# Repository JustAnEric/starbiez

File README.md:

# StarbieZ (star-beez)

Starbiez is a redo of the [Starbie](https://github.com/SharKingStudios/Starbie), and boy it packs *serious* power!

You're now getting your own extendible Tamagotchi that can run MANY things, basically sort of like a *Flipper Zero Nano* but without the pentesting tools! (don't go hacking things around town with this... :C)

## What it does

the ESP32-S3 Plus is where I'd start the shift from MCU to CPU, and it's the main driver for this project. With 16 MB of flash and 8 MB of RAM, it's way more than all the classic Tamagotchis that had **1 KB of RAM and ROM**! this Starbie is equipped with greater environmental awareness, audio and just *one more* button that adds so many more possibilities for what can be done with this project.

the environment can be currently measured by these sensors:

* a light dependent resistor on the right front face of the board
* a DHT11 humidity sensor on the top front face of the board
* AND a 6 pin IMU called the MPU6050 at the bottom right of the board!

the outputs on this device are *pretty simple*:
* 128x64 SSD1306 OLED screen
* buzzer/piezo

you provide input to this project by literally just clicking the cherry MX keyboard switches... and the circuitpython software being packaged for this project is considerably extendable being based off of the C++/.INO software. (yes, I'm rewriting/have rewritten it to make it easier for extensions, welcome beginners!)

## Bill of materials

| Part | What it's for | Qty | Unit | Total | Vendor |
| --- | --- | --- | --- | --- | --- |
| [ESP32-S3 Plus](https://www.pakronics.com.au/products/seeed-studio-xiao-esp32s3-plus-20-gpios-2-4ghz-wifi-ble-5-0-8mb-psram-16mb-flash-esp32-s3-dual-core-battery-charge-supported-ss102010671) | Main loop, more GPIO | 1 | $11.50 | $11.50 | [Pakronics](https://www.pakronics.com.au/products/seeed-studio-xiao-esp32s3-plus-20-gpios-2-4ghz-wifi-ble-5-0-8mb-psram-16mb-flash-esp32-s3-dual-core-battery-charge-supported-ss102010671) |
| [Gateron Milky Pro Switches (10pcs)](https://www.aliexpress.com/item/1005006425450443.html) | Switches and satisfying clicks | 1 | $1.06 | $1.06 | [AliExpress](https://www.aliexpress.com/item/1005006425450443.html) |
| [White 128x64 OLED display](https://www.aliexpress.com/item/1005004355547926.html) | The face of Starbiez | 1 | $2.85 | $2.85 | [AliExpress](https://www.aliexpress.com/item/1005004355547926.html) |
| [DHT22 Chip](https://core-electronics.com.au/dht22-temperature-and-relative-humidity-sensor-module.html) | For improved humidity sensing | 1 | $2.38 | $2.38 | [Core Electronics](https://core-electronics.com.au/dht22-temperature-and-relative-humidity-sensor-module.html) |
| [MPU6050 3-axis IMU](https://www.aliexpress.com/item/1005007989748804.html) | For shaking Starbiez | 1 | $2.92 | $2.92 | [Core Electronics](https://www.aliexpress.com/item/1005007989748804.html) |
| [600 Pack of 1/4 Watt 1% Resistors (30 values, 20 of each)](https://core-electronics.com.au/600-pack-of-1-4-watt-1-resistors-30-values-20-of-each.html) | For resistance in the circuit | 1 | $1.87 | $1.87 | [Core Electronics](https://core-electronics.com.au/600-pack-of-1-4-watt-1-resistors-30-values-20-of-each.html) |
| [Light dependent resistor](https://core-electronics.com.au/light-dependent-resistor-ldr.html) | For helping Starbiez sleep | 1 | $0.22 | $0.22 | [Core Electronics](https://core-electronics.com.au/light-dependent-resistor-ldr.html) |
| [Generic buzzer (⌀11 x 9)](https://core-electronics.com.au/piezo-buzzer.html) | For buzzing through menus (sound interactivity and accessibility) | 1 | $0.22 | $0.22 | [Core Electronics](https://core-electronics.com.au/piezo-buzzer.html) |
| [0.100" (2.54 mm) Female Header: 2x8-Pin, Straight](https://core-electronics.com.au/0-100-2-54-mm-female-header-2x8-pin-straight.html) | For GPIO connectivity (if anyone wanted to use this as a devboard) | 1 | $2.16 | $2.16 | [Core Electronics](https://core-electronics.com.au/0-100-2-54-mm-female-header-2x8-pin-straight.html) |
| [Mint Green MA Keycaps for MX Compatible Switches (5pcs)](https://core-electronics.com.au/mint-green-ma-keycaps-for-mx-compatible-switches-5-pack.html) | For topping off the Gateron Milky Pro Switches | 1 | $6.00 | $6.00 | [Core Electronics](https://core-electronics.com.au/mint-green-ma-keycaps-for-mx-compatible-switches-5-pack.html) |
| [JLCPCB Fab](https://jlcpcb.com) | Starbiez PCB | 1 | $11.95 | $11.95 | [JLCPCB](https://jlcpcb.com) |
| **Parts subtotal** | — | — | — | **$43.13** | — |
| **Tax & shipping** | — | — | — | **$27.33** | — |
| **Total** | — | — | — | **$70.46** | — |

## The process of building
### Day 1!

I spent the whole day, and I quite probably went past 4 hours (the actual making time of my board) to include the things that would make it my own...

You can see the **timestamps in the screenshot names**, for journal purposes I didn't replace them with a generic name throughout my processes!

How to interpret them:

* Example: `Screenshot 2026-10-06 064450.png`
* `2026-`: The year
* `10-`: The month
* `06`: The day
* `064450`:
    * `06`: The hour of the day (in AEST/AEDT, since I'm working on it in Australia/Sydney!)
    * `44`: The minute of the hour `06`
    * `50`: The seconds the screenshot was taken at

Hope this helps!

1. I created the project and crafted the schematic from the [tutorial](https://github.com/SharKingStudios/Starbie)

2. I laid out my PCB, creating the star `Edge.Cuts` from a reference image I found on Google first

    and then the satisfying ground layer by the B button...

    Those steps took about 4 hours and 5 minutes, timed by Google stopwatch (thanks search engine monopoly... never mind)

3. One of my first modifications was with changing the MCU from an ESP32-C3 to an ESP32-S3. My first strongest candidate.

    This swap didn't take very long... They're very structurally similar. I made sure to check Seeed's official guides though, just in case I got the pinouts wrong.

4. I included a second sensor, the LDR03 (light-dependent resistor is what LDR stands for) and I made sure to include a fixed resistance of 10kΩ, though this would change later down the track in my realisation an LDR03 is VERY hard to source in the real world today...!

    Here's where I put it, on the right wing of the star :)

5. A lot of organisation, and another output was added! A buzzer or a piezo was inspired by the Sprig's design when I made my Columns game for them (still waiting for approval), and I feel this Tamagotchi would do *really* well with a bit of tunes.

    I put in a little resistor to prevent any surge back to the tiny ESP... yeah it's pretty small.

6. I found a honeycomb SVG on Flaticon and I decided to use it for the two bottom corners of the board to add some more decoration!

    This was also the time I figured out how to get the 3D models into the footprints, I spent a long time trying to figure out how to get into the footprint editor...

7. Realizing there was not enough clearance for poor Switch 3 around J2, I had to make a few changes. And these changes would be for the better, it's now a dev board... :P It's when I made the switch to the ESP32-S3 Plus to get more GPIO. This is when my board started to look a lot more like trace spaghetti, but it's okay... (I am guessing)

    Now there's odd-even 2x8 GPIO female pins on the board, featuring these that go to the ESP32-S3 Plus! Go from right to left if you flip the Starbiez on it's right side:

    | Pin | GPIO |
    |-----|------|
    | 1 (right) | D6 |
    | 2 (left) | D7 |
    | 3 (right) | D10 |
    | 4 (left) | D11 |
    | 5 (right) | D12 |
    | 6 (left) | D13 |
    | 7 (right) | D14 |
    | 8 (left) | D15 |
    | 9 (right) | D16 |
    | 10 (left) | D17 |
    | 11 (right) | SDA (for I2C!) |
    | 12 (left) | D18 |
    | 13 (right) | SCL (for I2C!) |
    | 14 (left) | D19 |
    | 15 (right) | 3V3 output, make sure not to draw too much! |
    | 16 (left) | board GND |

    <details>
    <summary>Pin reference image for you nerds...</summary>

    > ## Front
    >
    > 
    >
    > ## Back
    > 

    </details>

    (*sparkles*!!) The sparkles I got from Claude, I asked it to make a flat monochrome white sparkle SVG graphic I could use... I plastered it onto the board on all the corners. (***THIS GRAPHIC IS NOW OUTSIDE OF THE FINAL REVISION DUE TO HALF LIFE REQUIREMENTS***)

8. Around this time, I was searching for good parts to use on AliExpress, but I found that shipping from China is a *little* bit too expensive for the grant I'm receiving. I then got a little distracted, still worrying myself about whether the light-dependent resistor I've wired up would be correct. More research got me to change it to a generic one, so here's the LDR part I recommend if anyone tries to build this project:

    | Specification | Value |
    |---------------|-------|
    | dark resistance (pitch black, 0 lux) | ~10MΩ |
    | light resistance (10 lux) | 8kΩ to 20kΩ |
    | max dissipation | 100mW
    | form factor | THT ~5mm |
    | ideally... | the GL5528 |

    I also switched the fixed resistance to 100kΩ so the ESP32-S3 Plus receives a more controlled value than in **0.03 V** or completely uncharted territory...

this took me the ENTIRETY of yesterday to build it and some of today to refine it, in retrospect I got up really early some days :| it took me about 1 hour and 22 minutes to write this writeup, according to Hackatime. I hope every viewer likes this project of mine!

### Day 2

I have swapped out the Claude star assets for my own as requested from Hack Club Half Life. It took about 45 minutes to draw the star assets in MS Paint.

I then converted these black paths into an SVG using Inkscape...

And afterwards, I redone the design of the silkscreen by my two hands. This took about 25 minutes.

I also added mounting holes in four places, as you can see.

### Final board renders (courtesy of JLC)

## Software

I extended/am extending CircuitPython for this project for providing user access to an API, you can view my extensions to CircuitPython [here](https://github.com/JustAnEric/starbiez-circuitpython)! It's recommended to use this instead of normal CircuitPython on your ESP32-S3, as you probably won't have access to much easy modifications.

## Ending README

hopefully Hack Club likes this little project of mine, so I can keep developing it more and more... I'm definitely pushing boundaries here with what can be done, but...

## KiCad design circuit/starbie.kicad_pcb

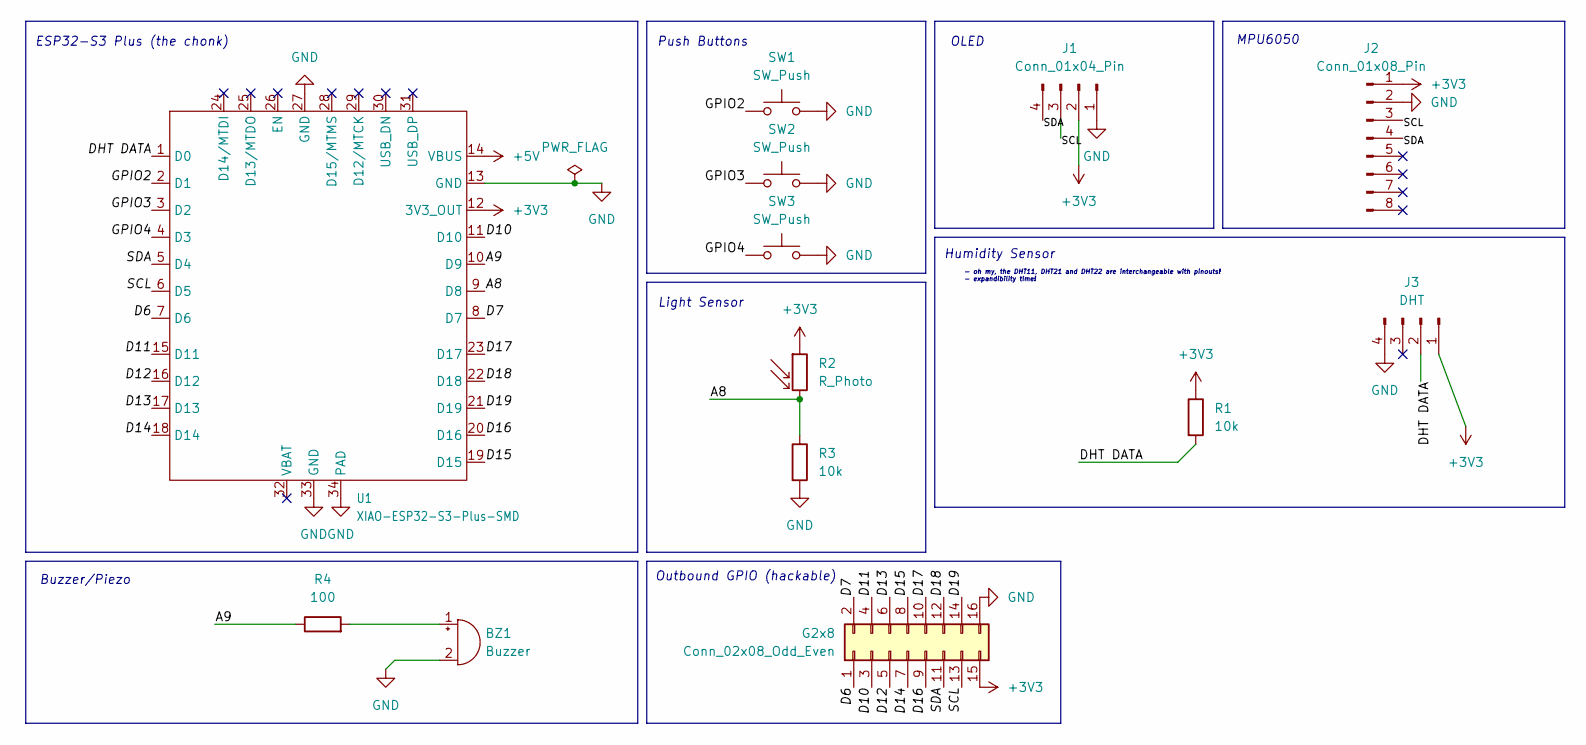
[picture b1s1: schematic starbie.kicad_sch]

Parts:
BZ1: Buzzer; Buzzer_12x9.5RM7.6
G2x8: Conn_02x08_Odd_Even; PinSocket_2x08_P2.54mm_Vertical
J1: Conn_01x04_Pin; Display_128x64_096_I2C
J2: Conn_01x08_Pin; MPU6050_Module
J3: DHT; PinSocket_1x04_P2.54mm_Vertical
R1, R3: 10k; R_Axial_DIN0204_L3.6mm_D1.6mm_P7.62mm_Horizontal
R2: R_Photo; R_LDR_4.9x4.2mm_P2.54mm_Vertical
R4: 100; R_Axial_DIN0204_L3.6mm_D1.6mm_P7.62mm_Horizontal
SW1, SW2, SW3: SW_Push; SW_Cherry_MX_1.00u_PCB
U1: XIAO-ESP32-S3-Plus-SMD

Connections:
+3V3: G2x8.15, J1.2, J2.1, J3.1, R1.1, R2.1, U1.12 (3V3_OUT); also elsewhere on the board
+5V: U1.14 (VBUS)
/A8: R2.2, R3.1, U1.9 (D8)
/A9: R4.1, U1.10 (D9)
/D6: G2x8.1, U1.7 (D6)
/D7: G2x8.2, U1.8 (D7)
/D10: G2x8.3, U1.11 (D10)
/D11: G2x8.4, U1.15 (D11)
/D12: G2x8.5, U1.16 (D12)
/D13: G2x8.6, U1.17 (D13)
/D14: G2x8.7, U1.18 (D14)
/D15: G2x8.8, U1.19 (D15)
/D16: G2x8.9, U1.20 (D16)
/D17: G2x8.10, U1.23 (D17)
/D18: G2x8.12, U1.22 (D18)
/D19: G2x8.14, U1.21 (D19)
/DHT DATA: J3.2, R1.2, U1.1 (D0); also elsewhere on the board
/GPIO2: SW1.1, U1.2 (D1)
/GPIO3: SW2.1, U1.3 (D2)
/GPIO4: SW3.1, U1.4 (D3)
/SCL: G2x8.13, J1.3, J2.3, U1.6 (D5)
/SDA: G2x8.11, J1.4, J2.4, U1.5 (D4)
GND: BZ1.2 (-), G2x8.16, J1.1, J2.2, J3.4, R3.2, SW1.2, SW2.2, SW3.2, U1.13 (GND), U1.27 (GND), U1.33 (GND), U1.34 (PAD); also elsewhere on the board
unnamed: BZ1.1 (+), R4.2

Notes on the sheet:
Outbound GPIO (hackable)
OLED
ESP32-S3 Plus (the chonk)
Buzzer/Piezo
Light Sensor
Push Buttons
Humidity Sensor
- oh my, the DHT11, DHT21 and DHT22 are interchangeable with pinouts! - expandibility time!
MPU6050

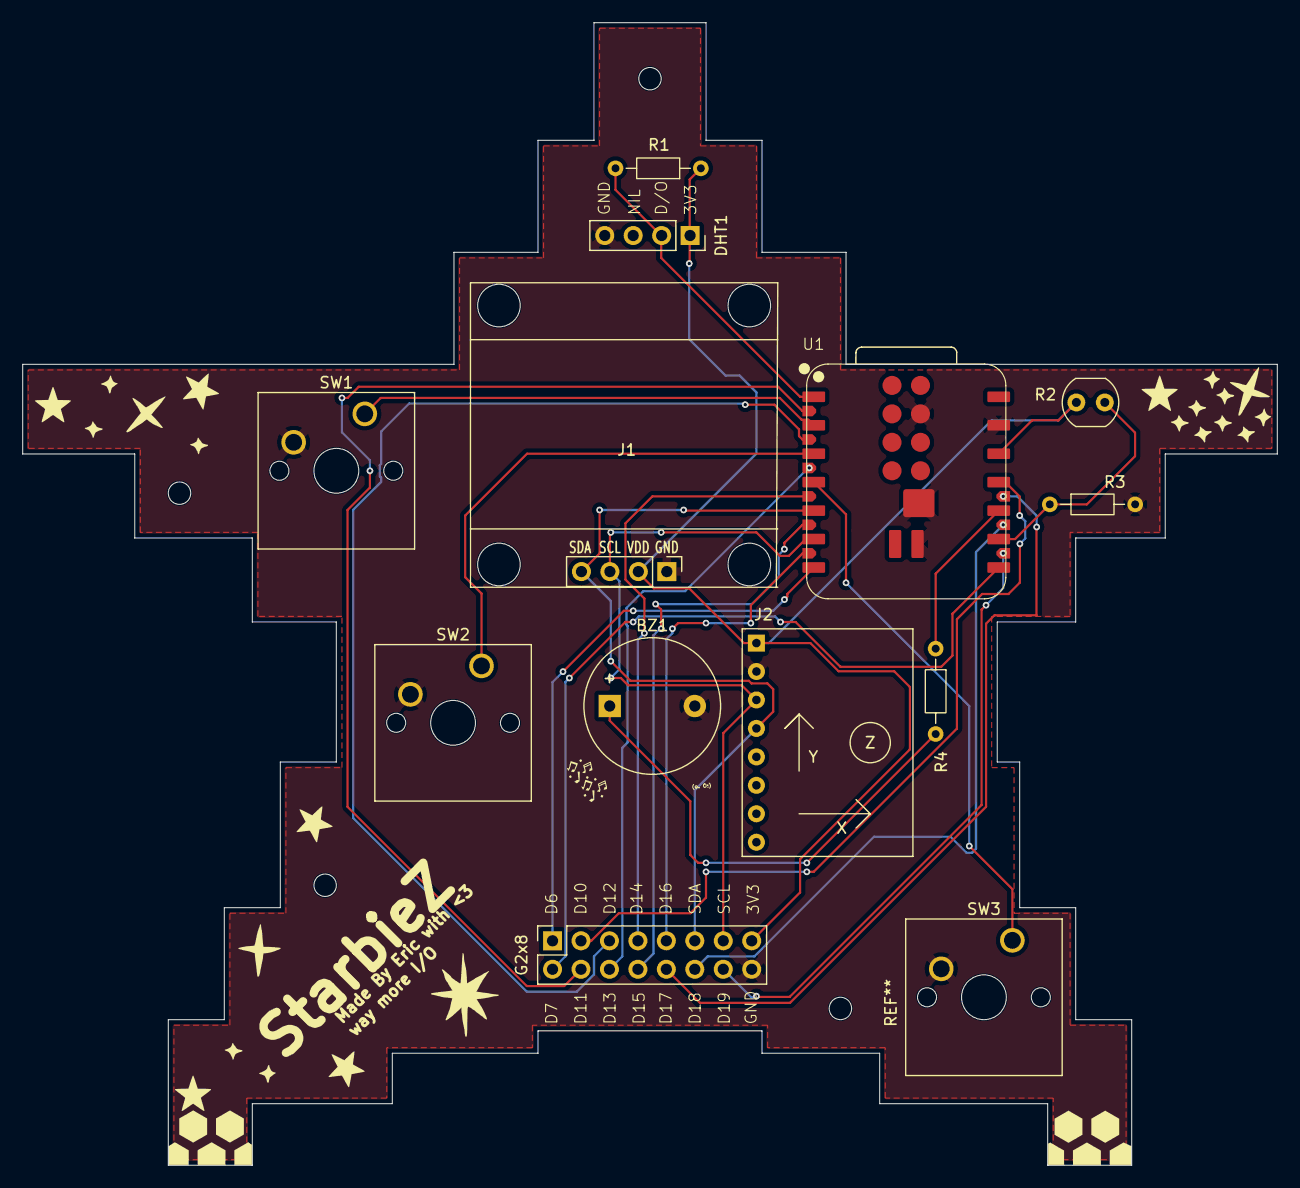
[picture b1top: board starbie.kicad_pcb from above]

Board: 2 copper layers, 112.0 x 102.0 mm, 13 parts (0 on the bottom side), 23 nets.

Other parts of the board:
DHT1: DHT; PinSocket_1x04_P2.54mm_Vertical

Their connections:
+3V3: DHT1.1; also elsewhere on the board
/DHT DATA: DHT1.2; also elsewhere on the board
GND: DHT1.4; also elsewhere on the board
